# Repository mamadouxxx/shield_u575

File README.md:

# Shield NUCLEO-U575ZI-Q

Shield fait sous KiCad 10 pour une carte NUCLEO-U575ZI-Q. Il se branche sur les connecteurs Zio de la Nucleo.

Il regroupe :
- un capteur SCD30 (CO₂, humidité, température), qu'on peut couper avec un TPS22918 pour économiser de l'énergie ;
- un petit écran OLED 0,96" en I2C ;
- un module radio 433 MHz (CC1101) en SPI ;
- une photorésistance pour mesurer la lumière ;
- 4 capteurs d'inclinaison pour savoir si on bouge l'appareil ;
- deux boutons.

Schéma : [schema.pdf](schema.pdf)

## Composants

- Capteur CO₂ Sensirion SCD30
- Interrupteur de charge TPS22918DBVR (SOT-23-6)
- Écran OLED Winstar WEA012864D (SSD1306)
- Module radio Ebyte E07-M1101D-SMA (CC1101) + antenne SMA 433 MHz
- Photorésistance GL5528
- 4 capteurs d'inclinaison SW-520D
- 2 boutons Omron B3F-1000
- Résistances et condensateurs CMS 0805
- Barrettes Zio pour la Nucleo, supports femelles 1×4, 1×7 et 2×4 pour les modules

## Brochage

| Fonction | Broches STM32 |
|---|---|
| SCD30 (I2C) | PC0 SCL, PC1 SDA, PF13 marche/arrêt |
| Écran (I2C) | PB8 SCL, PB9 SDA |
| Radio (SPI) | PA5 SCK, PA6 MISO, PA7 MOSI, PF12 CS, PA1 IRQ |
| Lumière, inclinaison | PC3 LUX (analogique), PD14 TILT |
| Boutons | PB6, PD15 |

Le circuit imprimé fait 2 couches et mesure 54 × 92 mm. Le routage est en cours.

## Licence

CERN-OHL-P v2, voir [LICENSE](LICENSE).

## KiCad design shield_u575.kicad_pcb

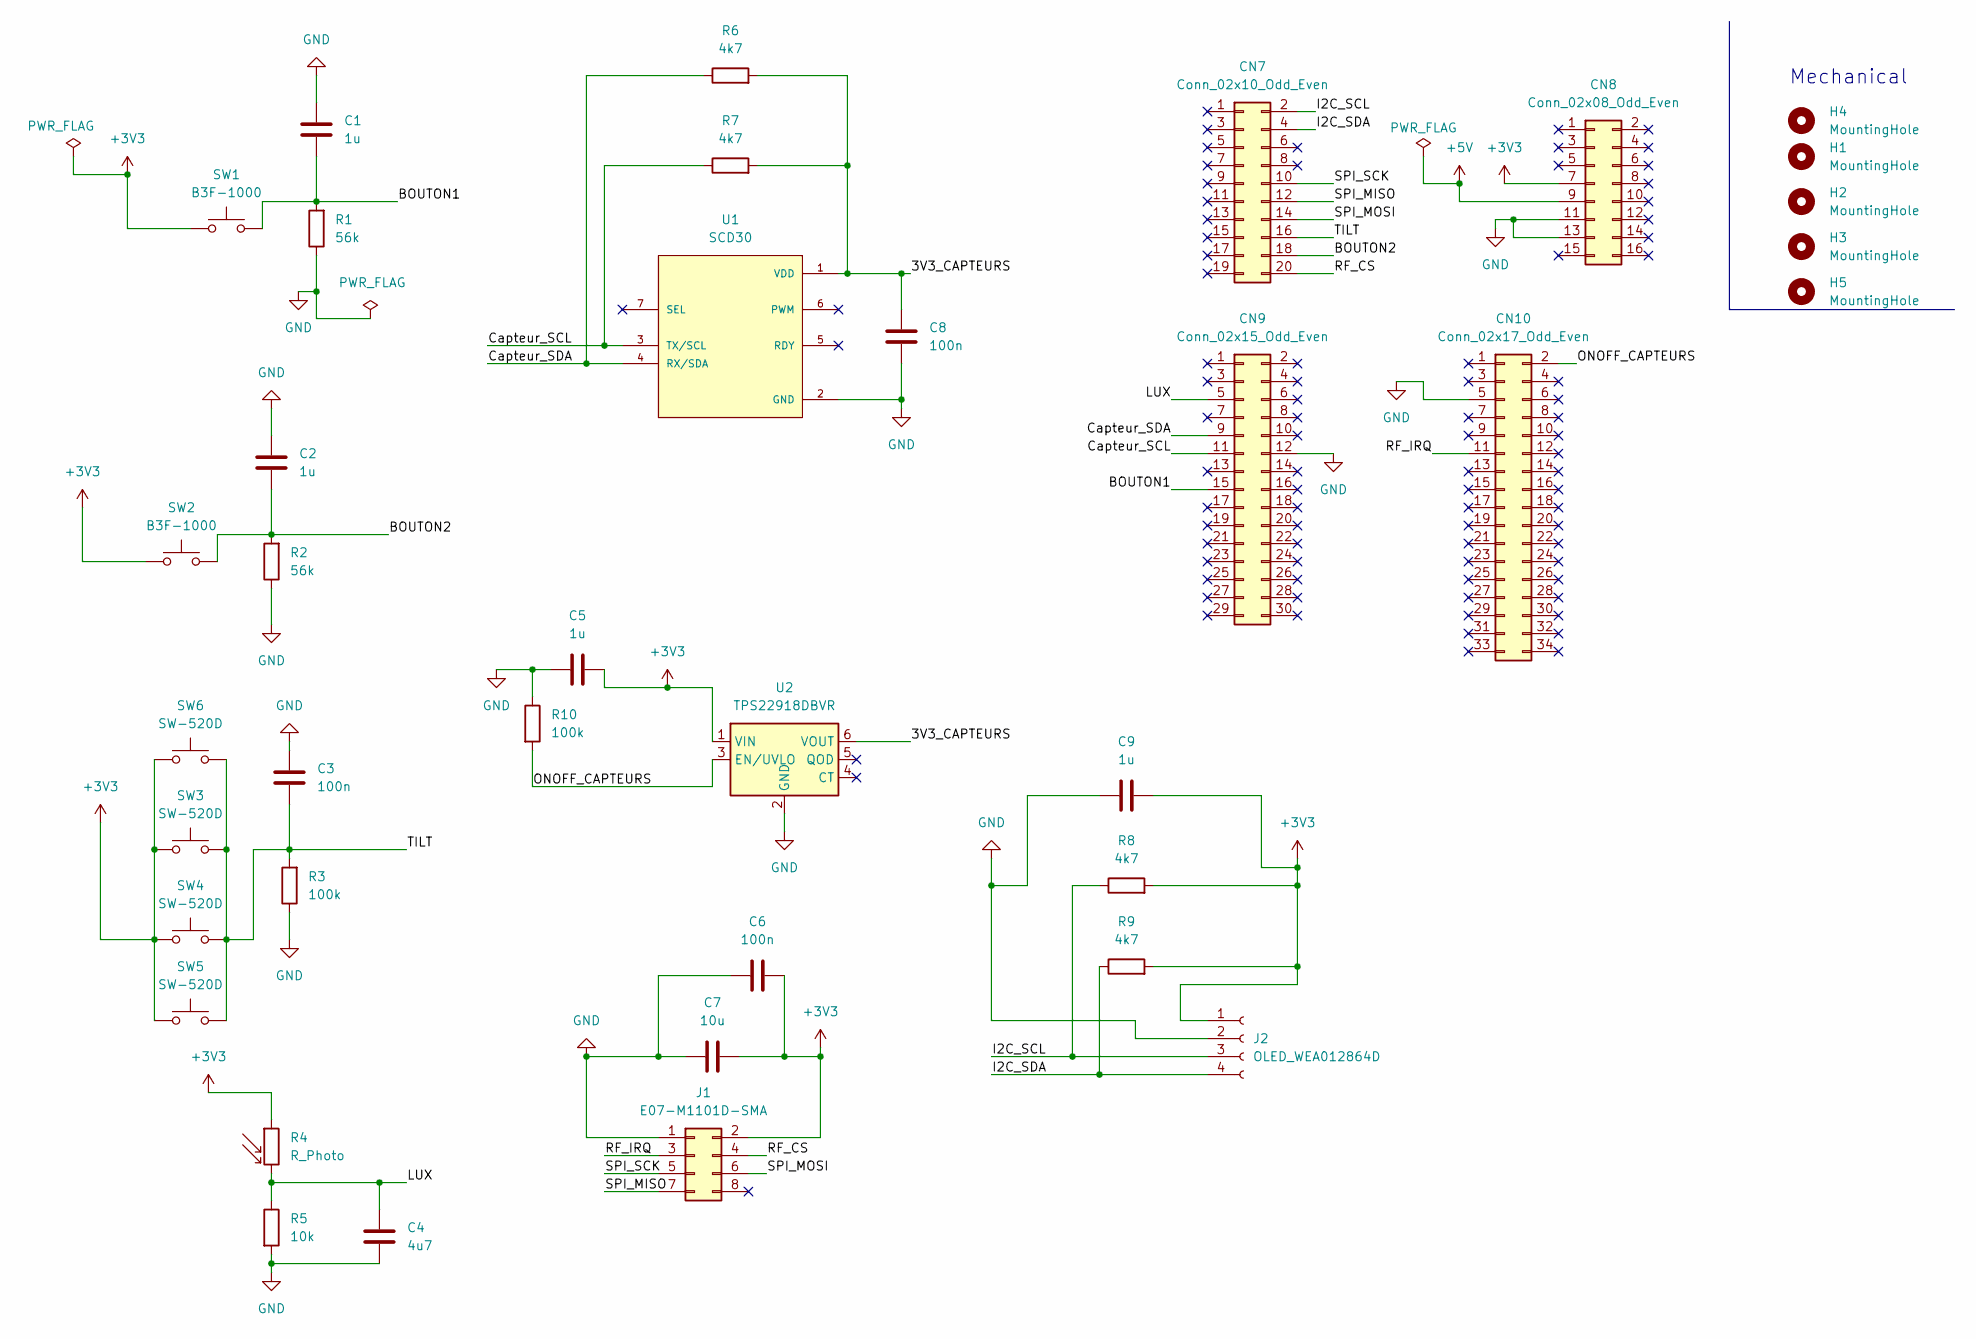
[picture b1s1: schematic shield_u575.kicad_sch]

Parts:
C1, C2, C5, C9: 1u; C_0805_2012Metric
C3, C6, C8: 100n; C_0805_2012Metric
C4: 4u7; C_0805_2012Metric
C7: 10u; C_0805_2012Metric
CN7: Conn_02x10_Odd_Even; PinHeader_2x10_P2.54mm_Vertical
CN8: Conn_02x08_Odd_Even; PinHeader_2x08_P2.54mm_Vertical
CN9: Conn_02x15_Odd_Even; PinHeader_2x15_P2.54mm_Vertical
CN10: Conn_02x17_Odd_Even; PinHeader_2x17_P2.54mm_Vertical
H1, H2, H3, H4, H5: MountingHole; MountingHole_3.2mm_M3
J1: E07-M1101D-SMA; PinHeader_2x04_P2.54mm_Vertical
J2: OLED_WEA012864D; PinSocket_1x04_P2.54mm_Vertical
R1, R2: 56k; R_0805_2012Metric
R3, R10: 100k; R_0805_2012Metric
R4: R_Photo; R_LDR_5.0x4.1mm_P3mm_Vertical
R5: 10k; R_0805_2012Metric
R6, R7, R8, R9: 4k7; R_0805_2012Metric
SW1, SW2: B3F-1000; SW_PUSH_6mm_H4.3mm
SW3, SW4, SW5, SW6: SW-520D; PinHeader_1x02_P2.54mm_Vertical
U1: SCD30; PinSocket_1x07_P2.54mm_Vertical; PARTREV D1
U2: TPS22918DBVR; SOT-23-6

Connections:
+3V3: C5.2, C6.1, C7.2, C9.1, CN8.7, J1.2, J2.1, R4.1, R8.2, R9.2, SW1.1, SW2.1, SW3.1, SW4.1, SW5.1, SW6.1, U2.1 (VIN)
+5V: CN8.9
/3V3_CAPTEURS: C8.1, R6.2, R7.2, U1.1 (VDD), U2.6 (VOUT)
/BOUTON1: C1.2, CN9.15, R1.2, SW1.2
/BOUTON2: C2.2, CN7.18, R2.2, SW2.2
/Capteur_SCL: CN9.11, R7.1, U1.3 (TX/SCL)
/Capteur_SDA: CN9.9, R6.1, U1.4 (RX/SDA)
/I2C_SCL: CN7.2, J2.3, R8.1
/I2C_SDA: CN7.4, J2.4, R9.1
/LUX: C4.1, CN9.5, R4.2, R5.1
/ONOFF_CAPTEURS: CN10.2, R10.2, U2.3 (EN/UVLO)
/RF_CS: CN7.20, J1.4
/RF_IRQ: CN10.11, J1.3
/SPI_MISO: CN7.12, J1.7
/SPI_MOSI: CN7.14, J1.6
/SPI_SCK: CN7.10, J1.5
/TILT: C3.2, CN7.16, R3.2, SW3.2, SW4.2, SW5.2, SW6.2
GND: C1.1, C2.1, C3.1, C4.2, C5.1, C6.2, C7.1, C8.2, C9.2, CN8.11, CN8.13, CN9.12, CN10.5, J1.1, J2.2, R1.1, R2.1, R3.1, R5.2, R10.1, U1.2 (GND), U2.2 (GND)

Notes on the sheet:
Mechanical

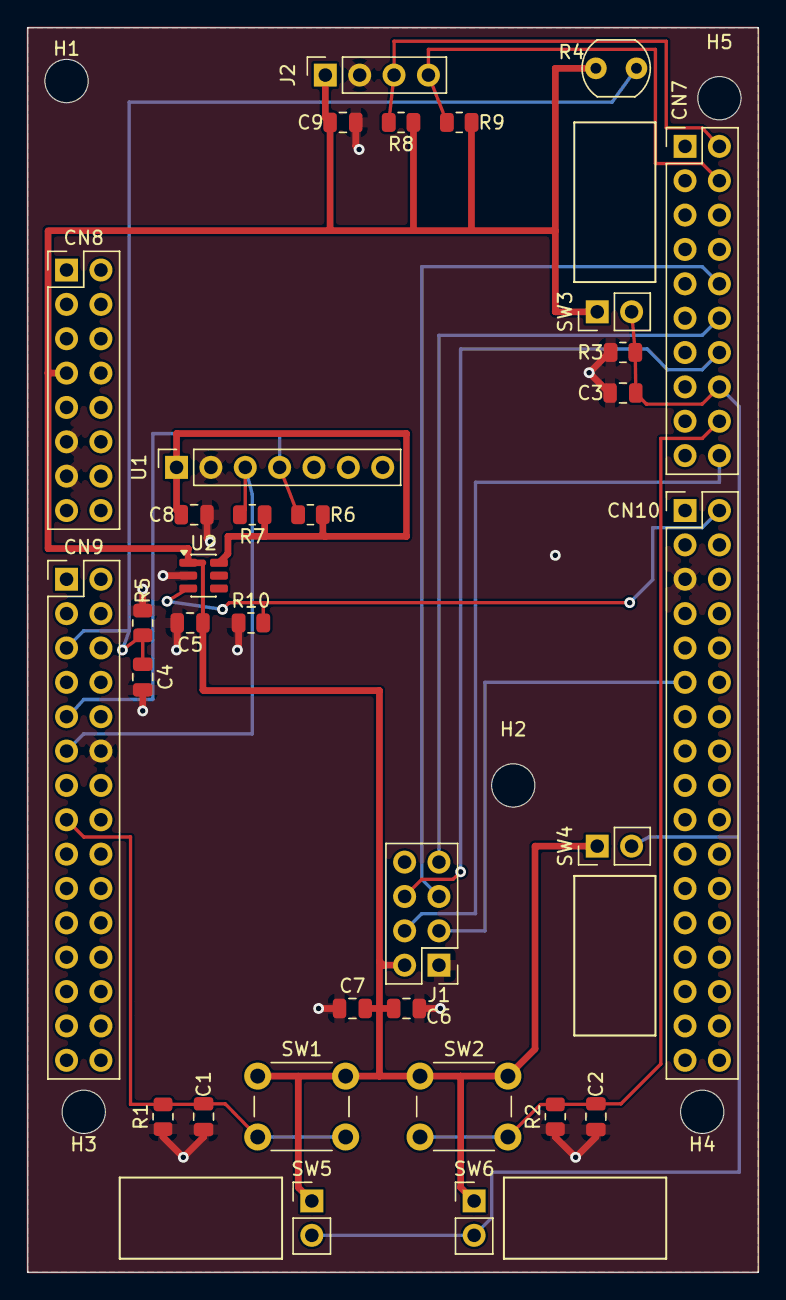
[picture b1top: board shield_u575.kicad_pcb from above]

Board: 2 copper layers, 54.0 x 92.0 mm, 38 parts (0 on the bottom side), 17 nets.

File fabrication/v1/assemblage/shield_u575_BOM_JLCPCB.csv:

Comment,Designator,Footprint,LCSC Part #
1uF 0805,"C1,C2,C5,C9",0805,
100nF 0805,"C3,C6,C8",0805,
4.7uF 0805,C4,0805,
10uF 0805,C7,0805,
56k 0805,"R1,R2",0805,
100k 0805,"R3,R10",0805,
10k 0805,R5,0805,
4.7k 0805,"R6,R7,R8,R9",0805,
TPS22810DBVR,U2,SOT-23-6,
